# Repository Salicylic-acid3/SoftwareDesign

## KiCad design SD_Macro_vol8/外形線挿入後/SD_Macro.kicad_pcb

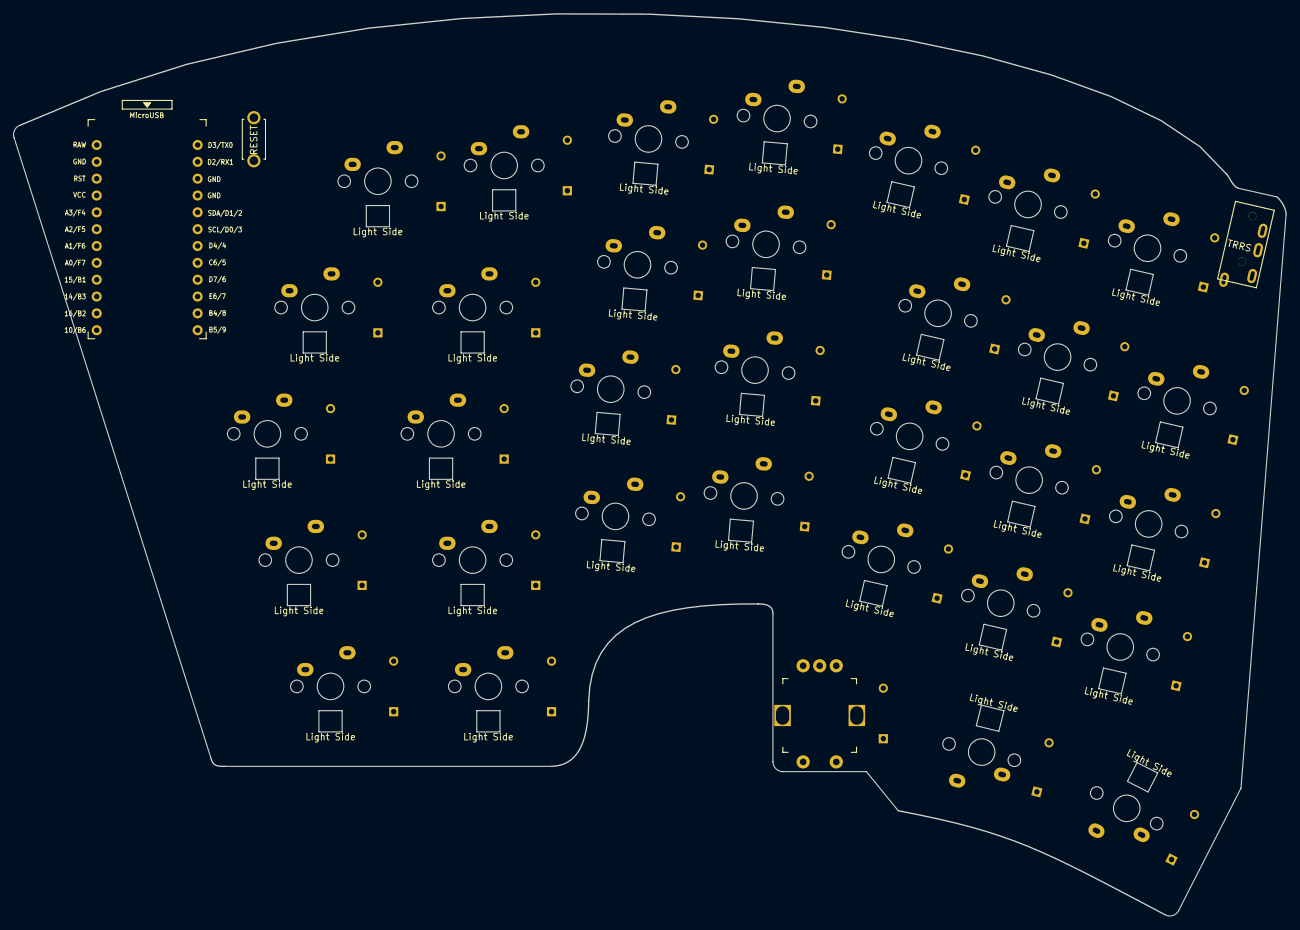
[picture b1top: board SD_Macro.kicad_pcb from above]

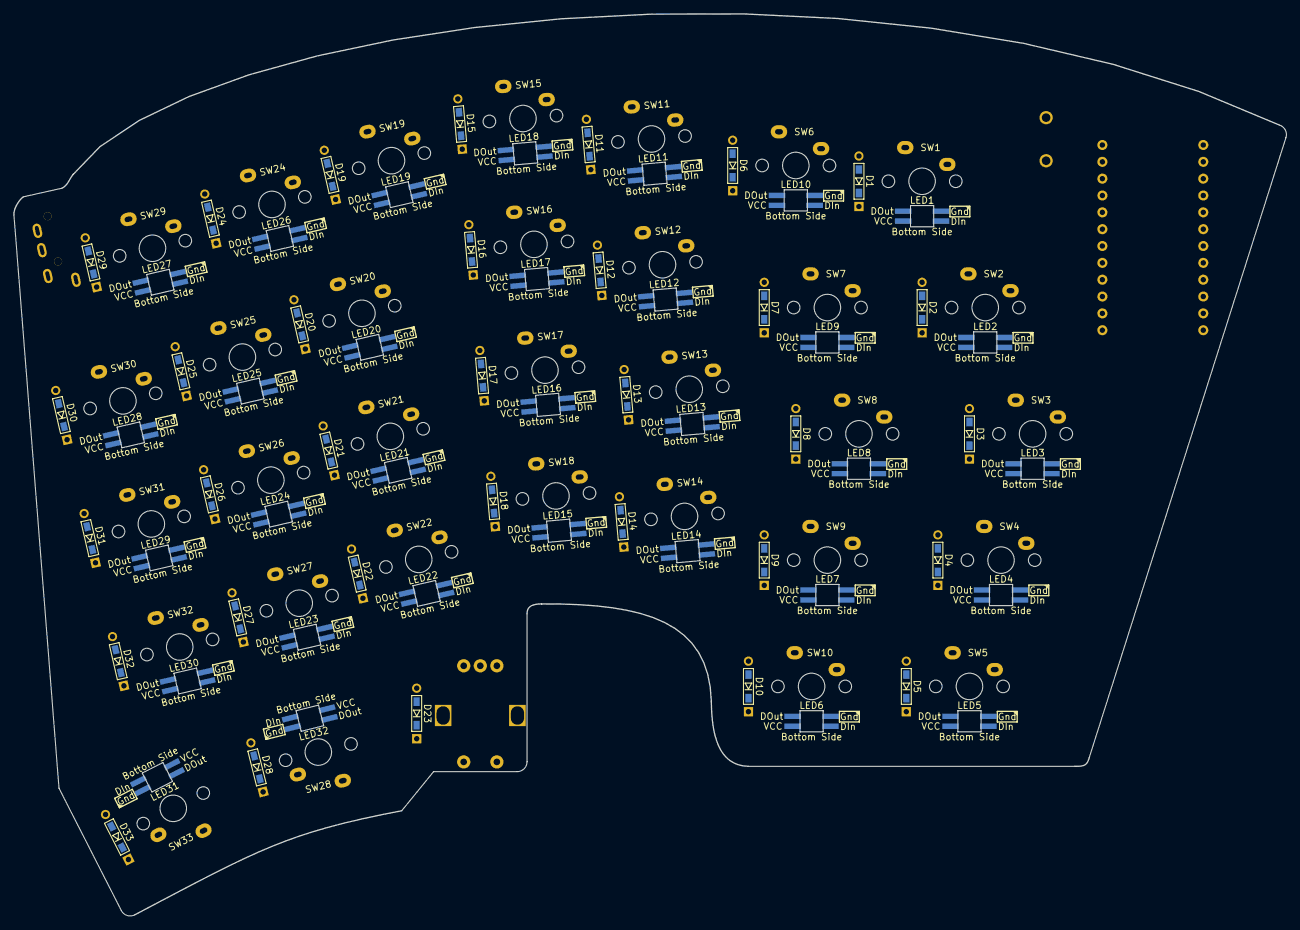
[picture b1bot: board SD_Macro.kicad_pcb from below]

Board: 2 copper layers, 191.9 x 136.0 mm, 101 parts (2 on the bottom side), 83 nets, no tracks yet.

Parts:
D1, D2, D3, D4, D5, D6, D7, D8, D9, D10, D11, D12, D13, D14, D15, D16, D17, D18, D19, D20, D21, D22, D23, D24, D25, D26, D27, D28, D29, D30, D31, D32, D33: D; Diode_TH_SMD
J1: TRRS_MJ-4PP-9
LED1, LED2, LED3, LED4, LED5, LED6, LED7, LED8, LED9, LED10, LED11, LED12, LED13, LED14, LED15, LED16, LED17, LED18, LED19, LED20, LED21, LED22, LED23, LED24, LED25, LED26, LED27, LED28, LED29, LED30, LED31, LED32: LED_SK6812MINI-E; LED_SK6812MINI-E_BL
SW1, SW6, SW7, SW8, SW9, SW11, SW12, SW13, SW14, SW15, SW16, SW17, SW18, SW19, SW20, SW21, SW22, SW24, SW25, SW26, SW27, SW28, SW29, SW30, SW31, SW32: SW_PUSH; CherryMX_1u_solder
SW2: SW_PUSH; CherryMX_1.5u_solder
SW3, SW4: SW_PUSH; CherryMX_1.75u_solder
SW5, SW10, SW33: SW_PUSH; CherryMX_1.25u_solder
SW23: Rotary_Encoder_Switch; RotaryEncoder_EC12E
SW34: SW_PUSH; ResetSW
U1: ProMicro; ProMicro_v3.5

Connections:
Col0: SW1.1, SW2.1, SW3.1, SW4.1, SW5.1, U1.20
Col1: SW6.1, SW7.1, SW8.1, SW9.1, SW10.1, U1.19
Col2: SW11.1, SW12.1, SW13.1, SW14.1, U1.18
Col3: SW15.1, SW16.1, SW17.1, SW18.1, U1.17
Col4: SW19.1, SW20.1, SW21.1, SW22.1, SW23.S2, U1.16
Col5: SW24.1, SW25.1, SW26.1, SW27.1, SW28.1, U1.15
Col6: SW29.1, SW30.1, SW31.1, SW32.1, SW33.1, U1.14
Data: J1.B, U1.2
GND: J1.C, LED1.2, LED2.2, LED3.2, LED4.2, LED5.2, LED6.2, LED7.2, LED8.2, LED9.2, LED10.2, LED11.2, LED12.2, LED13.2, LED14.2, LED15.2, LED16.2, LED17.2, LED18.2, LED19.2, LED20.2, LED21.2, LED22.2, LED23.2, LED24.2, LED25.2, LED26.2, LED27.2, LED28.2, LED29.2, LED30.2, LED31.2, LED32.2, SW23.C, SW34.2, U1.3, U1.4, U1.23
LED: LED1.3, U1.1
unnamed: D1.2, SW1.2
unnamed: D2.2, SW2.2
unnamed: D3.2, SW3.2
unnamed: D4.2, SW4.2
unnamed: D5.2, SW5.2
unnamed: D6.2, SW6.2
unnamed: D7.2, SW7.2
unnamed: D8.2, SW8.2
unnamed: D9.2, SW9.2
unnamed: D10.2, SW10.2
unnamed: D11.2, SW11.2
unnamed: D12.2, SW12.2
unnamed: D13.2, SW13.2
unnamed: D14.2, SW14.2
unnamed: D15.2, SW15.2
unnamed: D16.2, SW16.2
unnamed: D17.2, SW17.2
unnamed: D18.2, SW18.2
unnamed: D19.2, SW19.2
unnamed: D20.2, SW20.2
unnamed: D21.2, SW21.2
unnamed: D22.2, SW22.2
unnamed: D23.2, SW23.S1
unnamed: D24.2, SW24.2
unnamed: D25.2, SW25.2
unnamed: D26.2, SW26.2
unnamed: D27.2, SW27.2
unnamed: D28.2, SW28.2
unnamed: D29.2, SW29.2
unnamed: D30.2, SW30.2
unnamed: D31.2, SW31.2
unnamed: D32.2, SW32.2
unnamed: D33.2, SW33.2
unnamed: LED1.1, LED2.3
unnamed: LED2.1, LED3.3
unnamed: LED3.1, LED4.3
unnamed: LED4.1, LED5.3
unnamed: LED5.1, LED6.3
unnamed: LED6.1, LED7.3
unnamed: LED7.1, LED8.3
unnamed: LED8.1, LED9.3
unnamed: LED10.1, LED11.3
unnamed: LED9.1, LED10.3
unnamed: LED11.1, LED12.3
unnamed: LED12.1, LED13.3
unnamed: LED13.1, LED14.3
unnamed: LED14.1, LED15.3
unnamed: LED15.1, LED16.3
unnamed: LED16.1, LED17.3
unnamed: LED17.1, LED18.3
unnamed: LED18.1, LED19.3
unnamed: LED19.1, LED20.3
unnamed: LED20.1, LED21.3
unnamed: LED21.1, LED22.3
unnamed: LED22.1, LED23.3
unnamed: LED23.1, LED24.3
unnamed: LED24.1, LED25.3
unnamed: LED25.1, LED26.3
unnamed: LED26.1, LED27.3
unnamed: LED27.1, LED28.3
unnamed: LED28.1, LED29.3
unnamed: LED29.1, LED30.3
unnamed: LED30.1, LED31.3
unnamed: LED31.1, LED32.3
Reset: SW34.1, U1.22
RotaryA: SW23.A, U1.5
RotaryB: SW23.B, U1.6
Row0: D1.1, D6.1, D11.1, D15.1, D19.1, D24.1, D29.1, U1.7
Row1: D2.1, D7.1, D12.1, D16.1, D20.1, D25.1, D30.1, U1.8
Row2: D3.1, D8.1, D13.1, D17.1, D21.1, D26.1, D31.1, U1.9
Row3: D4.1, D9.1, D14.1, D18.1, D22.1, D27.1, D32.1, U1.10
Row4: D5.1, D10.1, D23.1, D28.1, D33.1, U1.11
VCC: J1.D, LED1.4, LED2.4, LED3.4, LED4.4, LED5.4, LED6.4, LED7.4, LED8.4, LED9.4, LED10.4, LED11.4, LED12.4, LED13.4, LED14.4, LED15.4, LED16.4, LED17.4, LED18.4, LED19.4, LED20.4, LED21.4, LED22.4, LED23.4, LED24.4, LED25.4, LED26.4, LED27.4, LED28.4, LED29.4, LED30.4, LED31.4, LED32.4, U1.13, U1.21

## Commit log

2021-08-14 キャッシュファイルを削除
2021-08-14 ライセンスを追加
2021-08-26 不要なファイルの削除
2021-10-08 回路図を諸々修正
    ・LED順を縦に修正
    ・TRRSジャックを追加
2021-10-14 連載7回目の教材を追加
    連載7回目の教材を追加
    ついでに不要なキャッシュファイルを削除
2021-11-24 連載8回目分を追加
2021-12-13 連載9回目分
2022-01-11 ProMicro の表裏を変更
2022-03-03 連載11回目分を追加
